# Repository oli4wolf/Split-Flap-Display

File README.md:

# Flap-Display
This Project is subdivided into different parts

* Initial Codebase of FAI for Toni Prototype
* The plan for a productline
* Project separating into Mechanical Topic, Electronical and Powersupply and the different variants.
** Mechanical Work
** Electronics and Powersupply
** Prototype Toni
** Simplistic Clock
** Complex Modul

# Initial Codebase can be found in this Folder. 
This folder contains the whole documentation with Protocol and manual that could be found and gathered. It's just a collection for historical purpose.
This was the beginning of the project. First it was just a clock from passionate Swiss Federal Railway person for home use. While the split-flap displays
where removed and replaced through digital displays with more flexible options. They created a clock that could be replicated, with the documentation in
French.
This initial work was used to create a gift for the new Boss of the Swiss Federal Railway responsible for person transportation (his name: Toni).
The gift had more capabilities (13x Alphabetic letters). The letter didn't work when the Gift was given.

# The plan for aproductline
A second wave of replacement was delayed and planned for 2019. At the same time an addition for the letters of Toni's variant was planned.
The idea is and was that the electro.-mechanical apprentice with the software apprentice create a second life for the Split-Flap displays.
These were removed and stored. Can be revamped by the electromechanical apprentice and put into a new frame with new electronics and
the more complex modules could be programmed by the software apprentice.
An initial Software can be found in this project. Additional functionality like Network connection or other are in the hand of the apprentices.
## Mechanical Work
(Todo: Topic of Rework anyway solution of split-flaps)
Tonis Gift was a wooden box, which can't be created for a bigger product. We can't create that much wooden box. So the idea is to have a metallic one.
(Todo: The box)
## Electronics and Powersupply
Im not that good in electronics. Therefore i based the rework on the prototype of Toni.
Powersupply stays the same. 
With all clocks we add two buttons (minutes +1, Hour +1).
Complex modules have an additional button (activate messages).

Different buttons have different issues. I added a capacitor to smooven the signal (which helps agains spurious signals).

### Prototype Toni
See initial Codebase

### Simplistic Clock

### Complex modules
See simplistic clock. Addtional i have added a buzzer and an additional button.

## Codebase
### Prototype Toni
See Initial Codebase
### Adding Letters

### Rework the code for simplistic clock

### Rework the code for MKR (Toni Variant)

# Known-Issues
* Somehow i have to have the end/begin of each signal send to a split-flap
* There is no feedback signal if the messages are on or off

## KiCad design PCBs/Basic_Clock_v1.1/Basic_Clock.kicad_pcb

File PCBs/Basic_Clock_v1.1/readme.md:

Version 1.1 Changes
* DIP for the RS485 Maxime microcontroller
* U-Numbers added
* Moved one wire 28v away from pin
* Changed Namings from GND to 0V

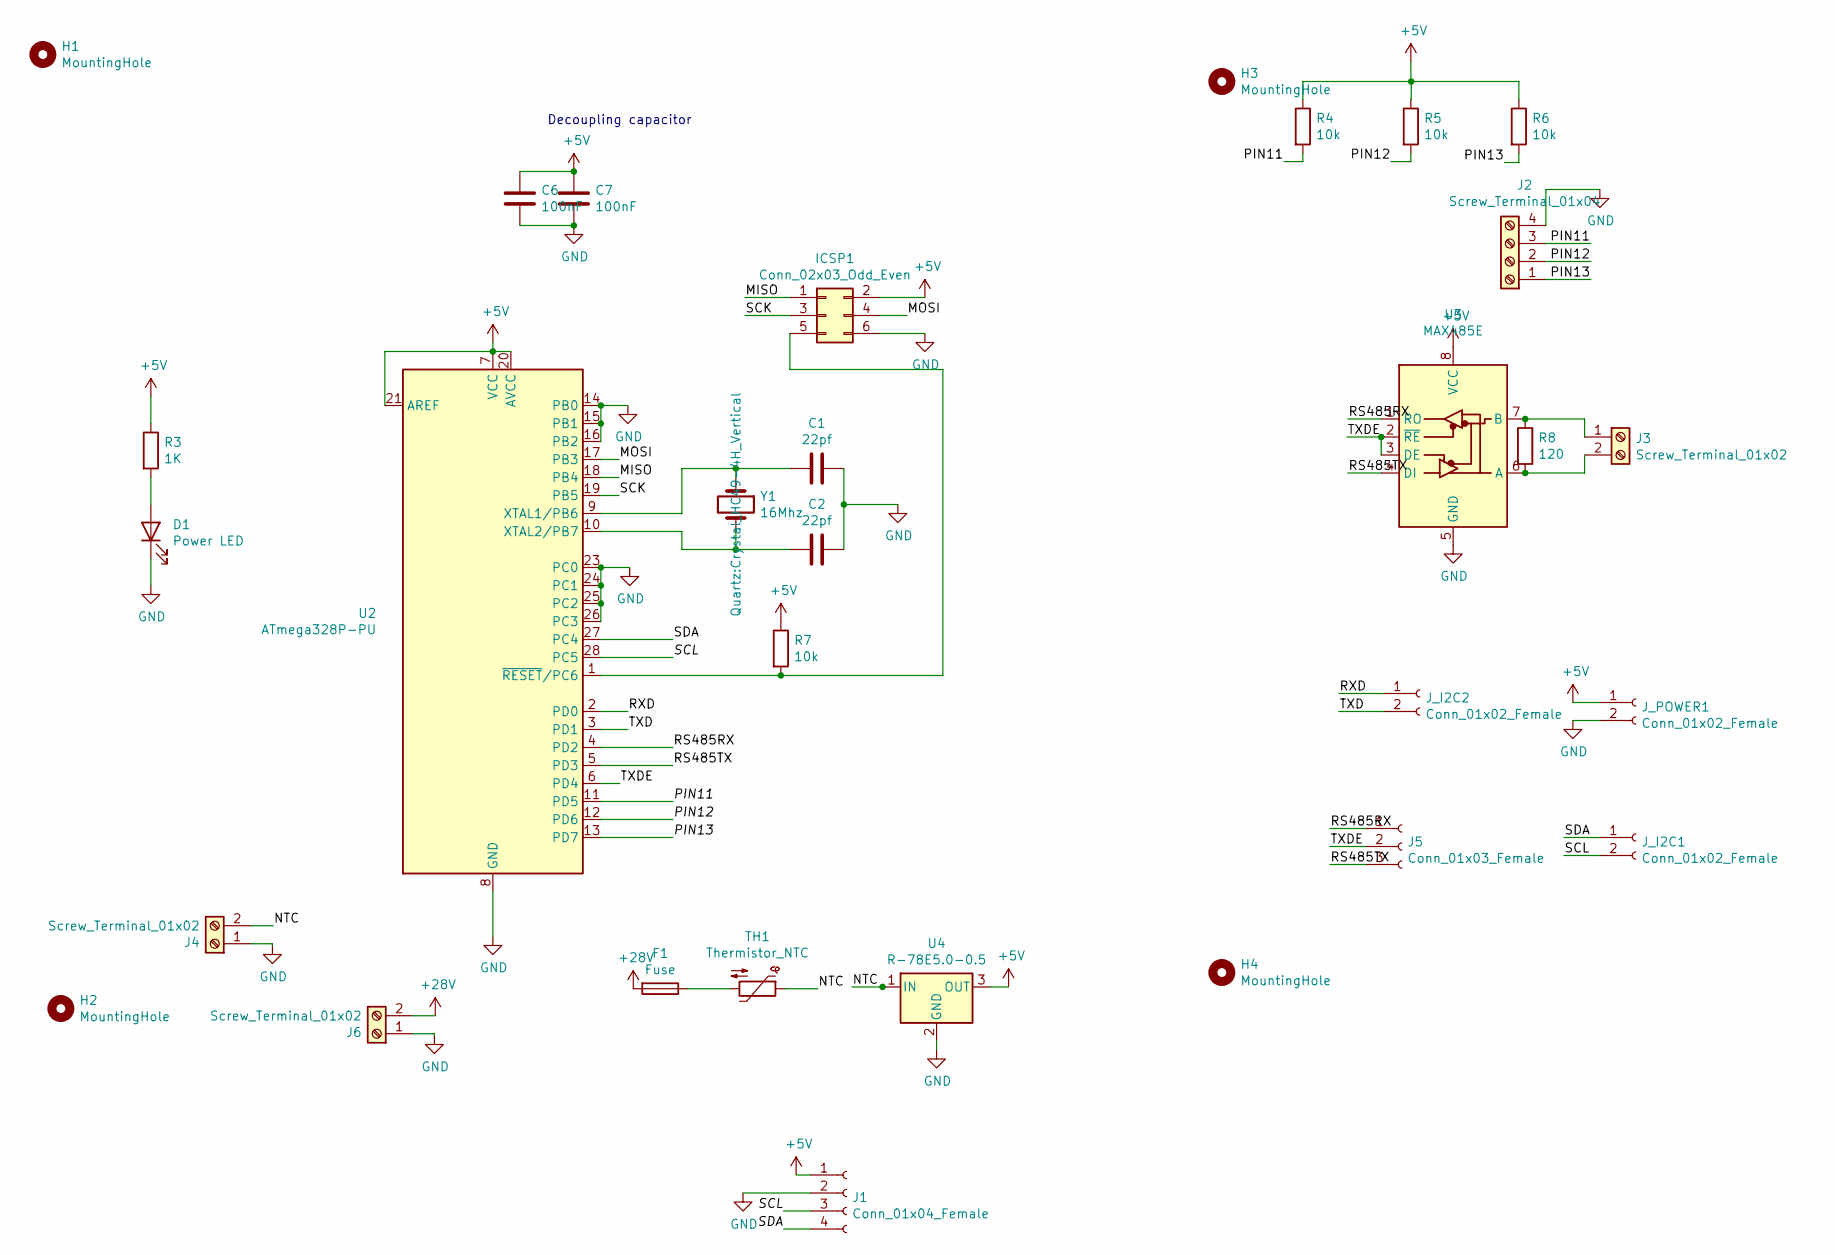
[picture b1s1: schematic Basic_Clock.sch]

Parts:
C1, C2: 22pf; C_Rect_L7.0mm_W3.5mm_P5.00mm
C6, C7: 100nF; C_Rect_L7.0mm_W3.5mm_P5.00mm
D1: Power LED; LED_D5.0mm_Clear
F1: Fuse; R_Axial_DIN0309_L9.0mm_D3.2mm_P12.70mm_Horizontal
H1, H2, H3, H4: MountingHole; MountingHole_3.2mm_M3_ISO14580
ICSP1: Conn_02x03_Odd_Even; PinSocket_2x03_P2.54mm_Vertical
J1: Conn_01x04_Female; PinSocket_1x04_P2.54mm_Vertical
J2: Screw_Terminal_01x04; TerminalBlock_RND_205-00234_1x04_P5.08mm_Horizontal
J3, J4, J6: Screw_Terminal_01x02; TerminalBlock_RND_205-00232_1x02_P5.08mm_Horizontal
J5: Conn_01x03_Female; PinSocket_1x03_P2.54mm_Vertical
J_I2C1, J_I2C2: Conn_01x02_Female; PinSocket_1x02_P2.54mm_Vertical
J_POWER1: Conn_01x02_Female; PinSocket_1x02_P2.54mm_Vertical
R3: 1K; R_Axial_DIN0309_L9.0mm_D3.2mm_P12.70mm_Horizontal
R4, R5, R6, R7: 10k; R_Axial_DIN0309_L9.0mm_D3.2mm_P12.70mm_Horizontal
R8: 120; R_Axial_DIN0309_L9.0mm_D3.2mm_P12.70mm_Horizontal
TH1: Thermistor_NTC; Crystal_HC49-4H_Vertical
U2: ATmega328P-PU; DIP-28_W7.62mm_Socket
U3: MAX485E; DIP-8_W7.62mm_Socket
U4: R-78E5.0-0.5; Converter_DCDC_RECOM_R-78E-0.5_THT
Y1: 16Mhz; Crystal_HC49-4H_Vertical

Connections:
+5V: C6.1, C7.1, ICSP1.2, J1.1, J_POWER1.1, R3.1, R4.1, R5.1, R6.1, R7.1, U2.7 (VCC), U2.20 (AVCC), U2.21 (AREF), U3.8 (VCC), U4.3 (OUT)
+28V: F1.2, J6.2
/MISO: ICSP1.1, U2.18 (PB4)
/MOSI: ICSP1.4, U2.17 (PB3)
/NTC: J4.2, TH1.1, U4.1 (IN)
/PIN11: J2.3, R4.2, U2.11 (PD5)
/PIN12: J2.2, R5.2, U2.12 (PD6)
/PIN13: J2.1, R6.2, U2.13 (PD7)
/RS485RX: J5.1, U2.4 (PD2), U3.1 (RO)
/RS485TX: J5.3, U2.5 (PD3), U3.4 (DI)
/RXD: J_I2C2.1, U2.2 (PD0)
/SCK: ICSP1.3, U2.19 (PB5)
/SCL: J1.3, J_I2C1.2, U2.28 (PC5)
/SDA: J1.4, J_I2C1.1, U2.27 (PC4)
/TXD: J_I2C2.2, U2.3 (PD1)
/TXDE: J5.2, U2.6 (PD4), U3.2 (~RE), U3.3 (DE)
GND: C1.1, C2.1, C6.2, C7.2, D1.1 (K), ICSP1.6, J1.2, J2.4, J4.1, J6.1, J_POWER1.2, U2.8 (GND), U2.14 (PB0), U2.15 (PB1), U2.16 (PB2), U2.22 (GND), U2.23 (PC0), U2.24 (PC1), U2.25 (PC2), U2.26 (PC3), U3.5 (GND), U4.2 (GND)
unnamed: C1.2, U2.9 (XTAL1/PB6), Y1.1
unnamed: C2.2, U2.10 (XTAL2/PB7), Y1.2
unnamed: D1.2 (A), R3.2
unnamed: F1.1, TH1.2
unnamed: ICSP1.5, R7.2, U2.1 (~RESET~/PC6)
unnamed: J3.1, R8.1, U3.7 (B)
unnamed: J3.2, R8.2, U3.6 (A)

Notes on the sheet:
Decoupling capacitor

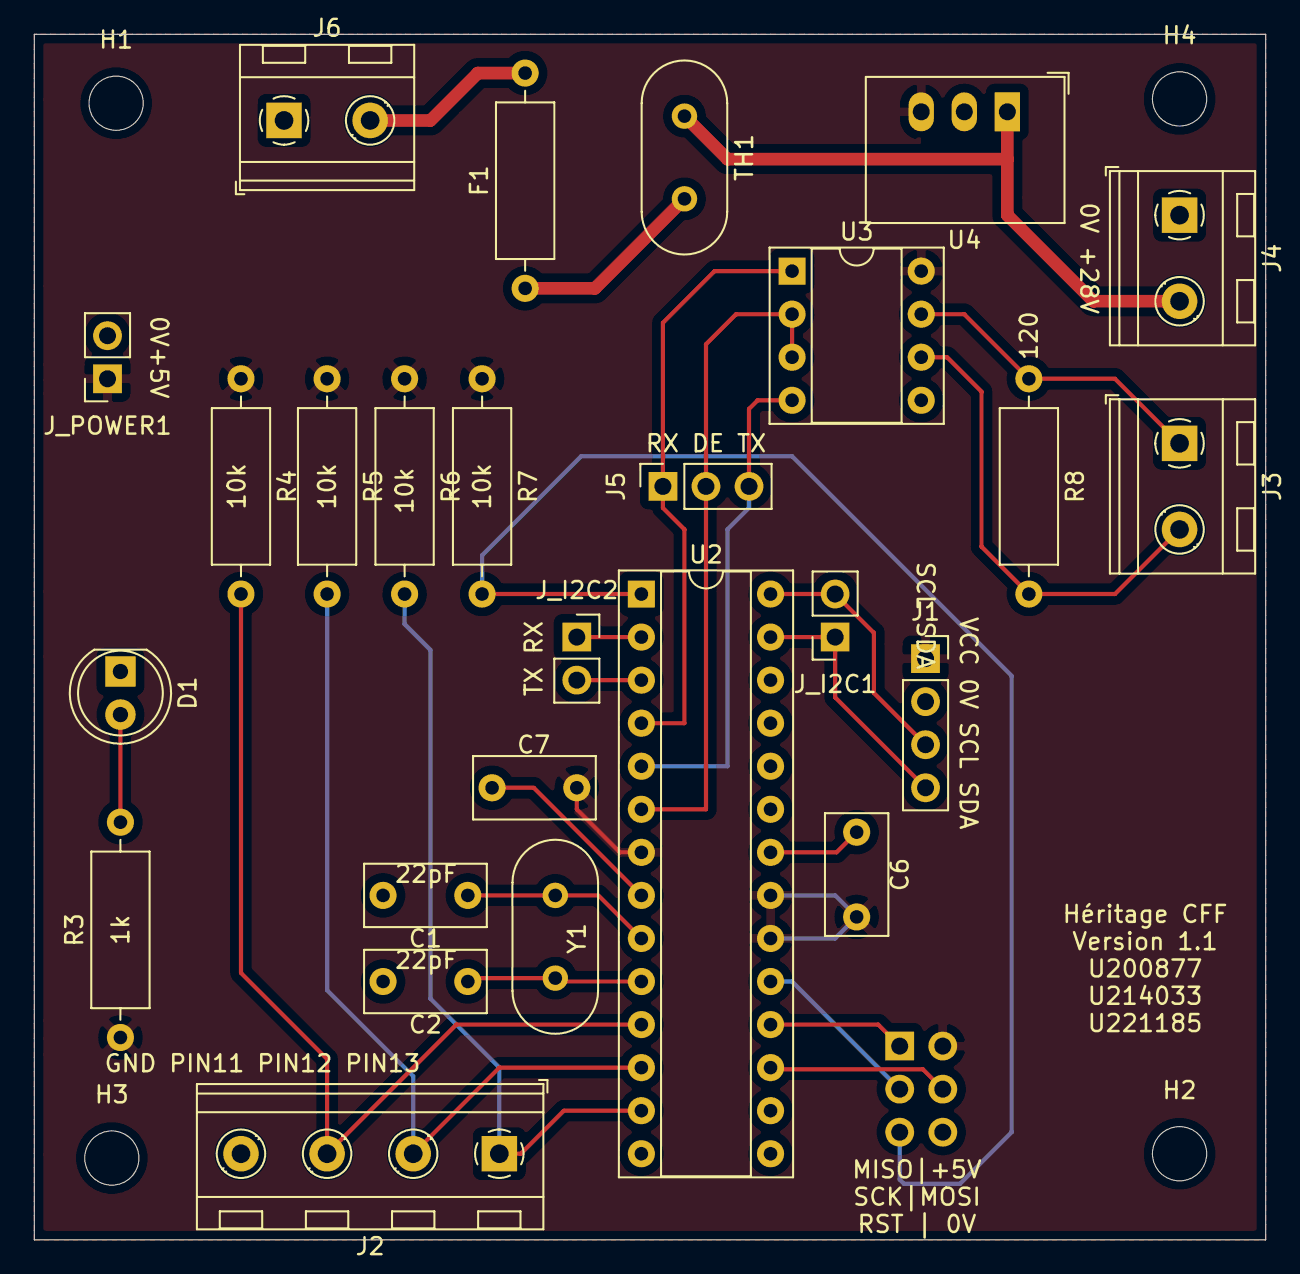
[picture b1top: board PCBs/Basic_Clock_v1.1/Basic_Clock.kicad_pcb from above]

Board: 2 copper layers, 72.6 x 71.1 mm, 31 parts (1 on the bottom side), 24 nets.

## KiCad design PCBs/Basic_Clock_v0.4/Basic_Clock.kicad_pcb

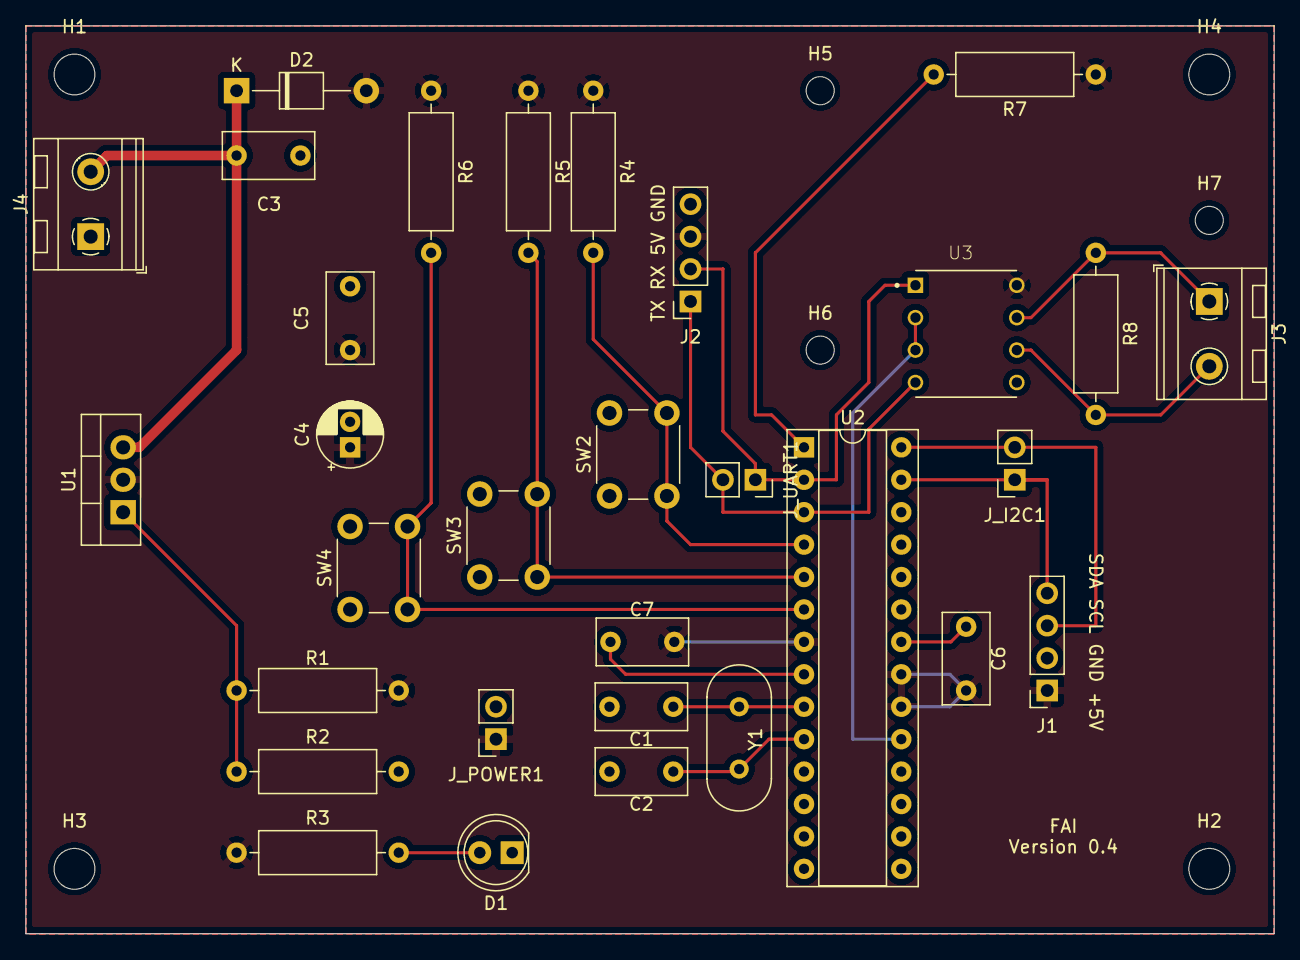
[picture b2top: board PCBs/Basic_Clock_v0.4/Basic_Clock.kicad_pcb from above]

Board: 2 copper layers, 97.8 x 71.1 mm, 38 parts (0 on the bottom side), 18 nets.

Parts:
C1, C2: 22pf; C_Rect_L7.0mm_W3.5mm_P5.00mm
C3, C5, C6, C7: 100nF; C_Rect_L7.0mm_W3.5mm_P5.00mm
C4: 1uF; CP_Radial_D5.0mm_P2.00mm
D1: Power LED; LED_D5.0mm_Clear
D2: D; D_T-1_P10.16mm_Horizontal
H1, H2, H3, H4: MountingHole; MountingHole_3.2mm_M3_ISO14580
H5, H6, H7: MountingHole; MountingHole_2.2mm_M2_ISO14580
J1, J2: Conn_01x04_Female; PinSocket_1x04_P2.54mm_Vertical
J3, J4: Screw_Terminal_01x02; TerminalBlock_RND_205-00232_1x02_P5.08mm_Horizontal
J_I2C1: Conn_01x02_Female; PinSocket_1x02_P2.54mm_Vertical
J_POWER1: Conn_01x02_Female; PinSocket_1x02_P2.54mm_Vertical
J_UART1: Conn_01x02_Female; PinSocket_1x02_P2.54mm_Vertical
R1: 240; R_Axial_DIN0309_L9.0mm_D3.2mm_P12.70mm_Horizontal
R2: 720; R_Axial_DIN0309_L9.0mm_D3.2mm_P12.70mm_Horizontal
R3: 1K; R_Axial_DIN0309_L9.0mm_D3.2mm_P12.70mm_Horizontal
R4, R5, R6, R7: 10k; R_Axial_DIN0309_L9.0mm_D3.2mm_P12.70mm_Horizontal
R8: 120; R_Axial_DIN0309_L9.0mm_D3.2mm_P12.70mm_Horizontal
SW2, SW3, SW4: SW_Push; SW_PUSH_6mm_H5mm
U1: LM317_TO-220; TO-220-3_Vertical
U2: ATmega328P-PU; DIP-28_W7.62mm_Socket
U3: MAX485E; DIP794W47P254L991H457Q8
Y1: 16Mhz; Crystal_HC49-4H_Vertical

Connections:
+5V: C4.1, C5.1, C6.1, C7.1, D2.2, J1.1, J2.3, J_POWER1.1, R1.1, R3.1, R4.1, R5.1, R6.1, R7.1, U1.2, U2.7, U2.20, U2.21, U3.8
+28V: C3.1, D2.1, J4.2, U1.3
/PIN2: R4.2, SW2.2, U2.4
/PIN3: R5.2, SW3.2, U2.5
/PIN4: R6.2, SW4.2, U2.6
/RX: J2.2, J_UART1.1, U2.2, U3.1
/SCL: J1.3, J_I2C1.2, U2.28
/SDA: J1.4, J_I2C1.1, U2.27
/TX: J2.1, J_UART1.2, U2.3, U3.4
/TXDE: U2.19, U3.2, U3.3
GND: C1.1, C2.1, C3.2, C4.2, C5.2, C6.2, C7.2, D1.1, J1.2, J2.4, J4.1, J_POWER1.2, R2.2, SW2.1, SW3.1, SW4.1, U2.8, U2.11, U2.12, U2.13, U2.14, U2.15, U2.16, U2.17, U2.18, U2.22, U2.23, U2.24, U2.25, U2.26, U3.5
unnamed: C1.2, U2.9, Y1.1
unnamed: C2.2, U2.10, Y1.2
unnamed: D1.2, R3.2
unnamed: J3.1, R8.1, U3.7
unnamed: J3.2, R8.2, U3.6
unnamed: R1.2, R2.1, U1.1
unnamed: R7.2, U2.1

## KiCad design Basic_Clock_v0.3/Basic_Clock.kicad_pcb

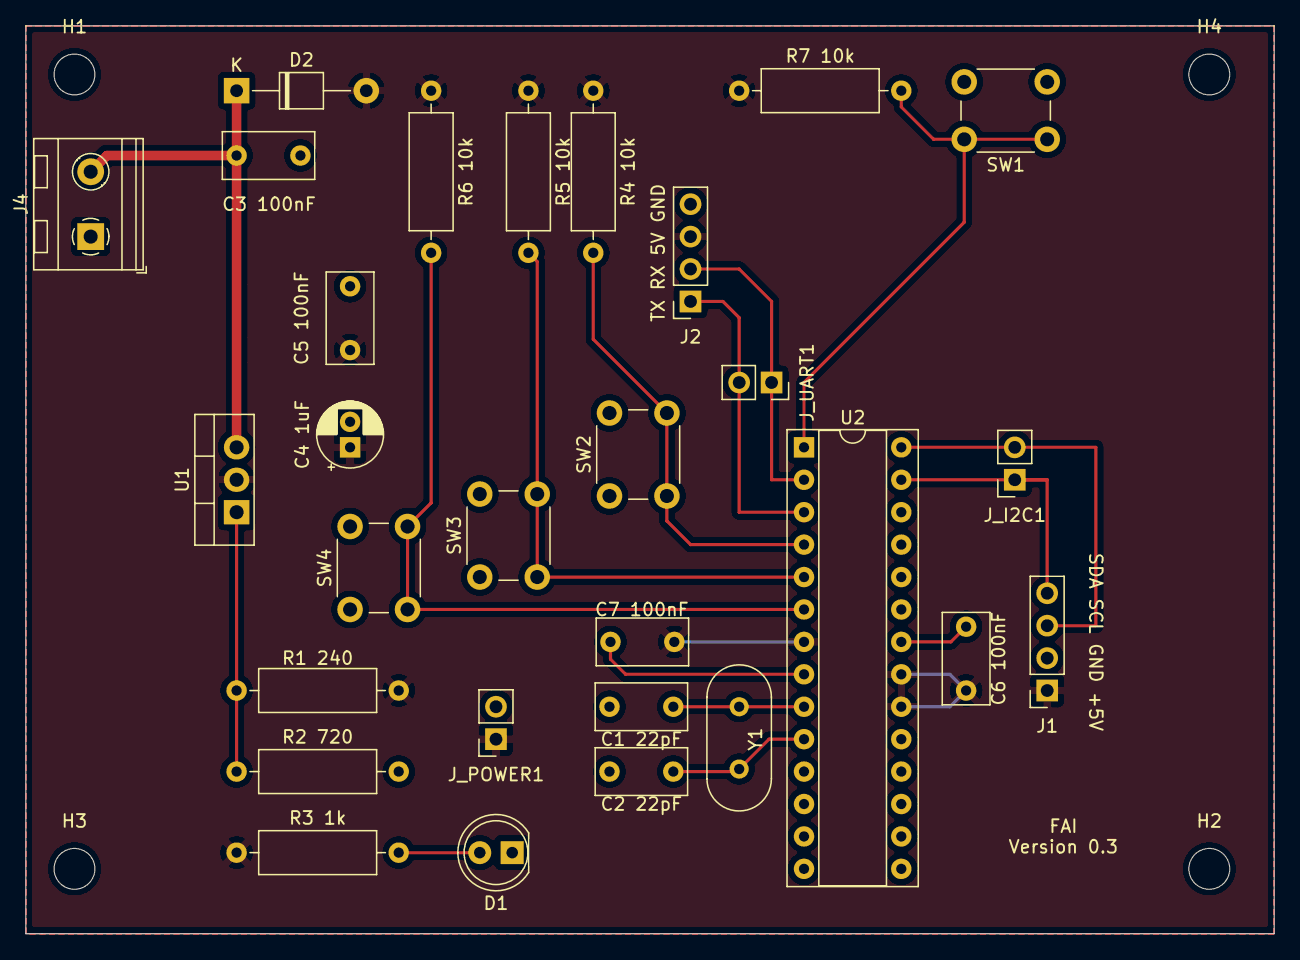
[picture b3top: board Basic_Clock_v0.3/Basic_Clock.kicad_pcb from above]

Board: 2 copper layers, 97.8 x 71.1 mm, 33 parts (0 on the bottom side), 15 nets.

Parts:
C1 22pF, C2 22pF: 22pf; C_Rect_L7.0mm_W3.5mm_P5.00mm
C3 100nF, C5 100nF, C6 100nF, C7 100nF: 100nF; C_Rect_L7.0mm_W3.5mm_P5.00mm
C4 1uF: 1uF; CP_Radial_D5.0mm_P2.00mm
D1: Power LED; LED_D5.0mm_Clear
D2: D; D_T-1_P10.16mm_Horizontal
H1, H2, H3, H4: MountingHole; MountingHole_3.2mm_M3_ISO14580
J1, J2: Conn_01x04_Female; PinSocket_1x04_P2.54mm_Vertical
J4: Screw_Terminal_01x02; TerminalBlock_RND_205-00232_1x02_P5.08mm_Horizontal
J_I2C1: Conn_01x02_Female; PinSocket_1x02_P2.54mm_Vertical
J_POWER1: Conn_01x02_Female; PinSocket_1x02_P2.54mm_Vertical
J_UART1: Conn_01x02_Female; PinSocket_1x02_P2.54mm_Vertical
R1 240: 240; R_Axial_DIN0309_L9.0mm_D3.2mm_P12.70mm_Horizontal
R2 720: 720; R_Axial_DIN0309_L9.0mm_D3.2mm_P12.70mm_Horizontal
R3 1k: 1K; R_Axial_DIN0309_L9.0mm_D3.2mm_P12.70mm_Horizontal
R4 10k, R5 10k, R6 10k, R7 10k: 10k; R_Axial_DIN0309_L9.0mm_D3.2mm_P12.70mm_Horizontal
SW1: SW_Push_Reset; SW_PUSH_6mm_H5mm
SW2, SW3, SW4: SW_Push; SW_PUSH_6mm_H5mm
U1: LM317_TO-220; TO-220-3_Vertical
U2: ATmega328P-PU; DIP-28_W7.62mm_Socket
Y1: 16Mhz; Crystal_HC49-4H_Vertical

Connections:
+5V: C4 1uF.1, C5 100nF.1, C6 100nF.1, C7 100nF.1, D2.2, J1.1, J2.3, J_POWER1.1, R1 240.1, R3 1k.1, R4 10k.1, R5 10k.1, R6 10k.1, R7 10k.1, U1.2, U2.7, U2.20, U2.21
+28V: C3 100nF.1, D2.1, J4.2, U1.3
/PIN2: R4 10k.2, SW2.2, U2.4
/PIN3: R5 10k.2, SW3.2, U2.5
/PIN4: R6 10k.2, SW4.2, U2.6
/RX: J2.2, J_UART1.1, U2.2
/SCL: J1.3, J_I2C1.2, U2.28
/SDA: J1.4, J_I2C1.1, U2.27
/TX: J2.1, J_UART1.2, U2.3
GND: C1 22pF.1, C2 22pF.1, C3 100nF.2, C4 1uF.2, C5 100nF.2, C6 100nF.2, C7 100nF.2, D1.1, J1.2, J2.4, J4.1, J_POWER1.2, R2 720.2, SW1.2, SW2.1, SW3.1, SW4.1, U2.8, U2.11, U2.12, U2.13, U2.14, U2.15, U2.16, U2.17, U2.18, U2.19, U2.22, U2.23, U2.24, U2.25, U2.26
unnamed: C1 22pF.2, U2.9, Y1.1
unnamed: C2 22pF.2, U2.10, Y1.2
unnamed: D1.2, R3 1k.2
unnamed: R1 240.2, R2 720.1, U1.1
unnamed: R7 10k.2, SW1.1, U2.1

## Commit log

2020-02-02 Initial commit. Initial code from Toni and documentation. Initial code with added messages. New MKR based Version with buttons.
2020-08-23 Initial Version of the MKR Clock for the Demo.
2020-08-23 Removed unused code Clutter.
2020-09-14 First draft for the PCB.
2020-09-14 Footprint somehow changed? Fixed and routed the missing with VIAs.
2020-09-15 Revisioned after Feedback from Frank.
2020-09-16 Created Gerber files Updated Components
2020-09-28 Clock Version 0.2
2020-10-09 Code Version intermediate.
2020-10-23 New Version 0.3
2020-10-26 New Testprogram Reorganized Folder
2020-11-01 Added PCB Version 4 Removed Gerberfiles and drill files
2020-11-03 PCB Version 0.5
2020-11-03 Move to a folder
2020-11-04 Update after Feedback.
2020-11-09 PCB 0.6 Fixed inscription Software to test with running.
2020-11-21 PCB Version validated with the Addresses and Positions as configured.
2020-11-21 Final version PCB
2020-11-21 Fixed ICSP Pinout
2020-11-25 PCB latest version.
2020-11-25 Latest Program.
2020-12-14 KiCad Version 1.1 added NTC and Fuse.
